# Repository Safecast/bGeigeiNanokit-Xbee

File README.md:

# bGeigieCast

Available at [Link](https://bgeigiezen.safecast.jp/store-2/bgeigienano/)

* An extension module to use your mobile bGeigieNano as a fixed sensor! 
* Adds Wi-Fi and Bluetooth (BLE) to a bGeigieNano.
* Open Source software and Open Source hardware. 
* For real-time reporting/sending data to the Safecast API in fixed and mobile mode.
* Easy to program and change code for other APIs due to the USB-C connector.
* Needs to be soldered together to use it.

User manual and other documentation on the Github Wiki:

* [User manual](https://github.com/Safecast/bGeigieCast/wiki/User-manual)
* [Quick start guide](https://github.com/Safecast/bGeigieCast/wiki/Quick-start-guide)
* [Set up your development environment](https://github.com/Safecast/bGeigieCast/wiki/Development-environment)

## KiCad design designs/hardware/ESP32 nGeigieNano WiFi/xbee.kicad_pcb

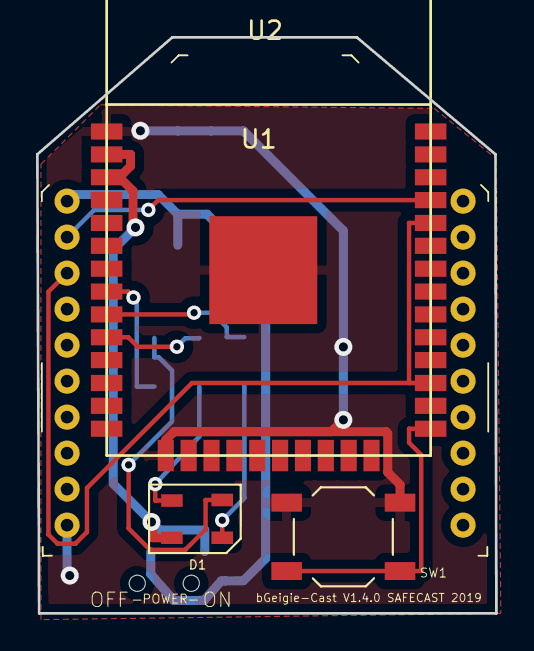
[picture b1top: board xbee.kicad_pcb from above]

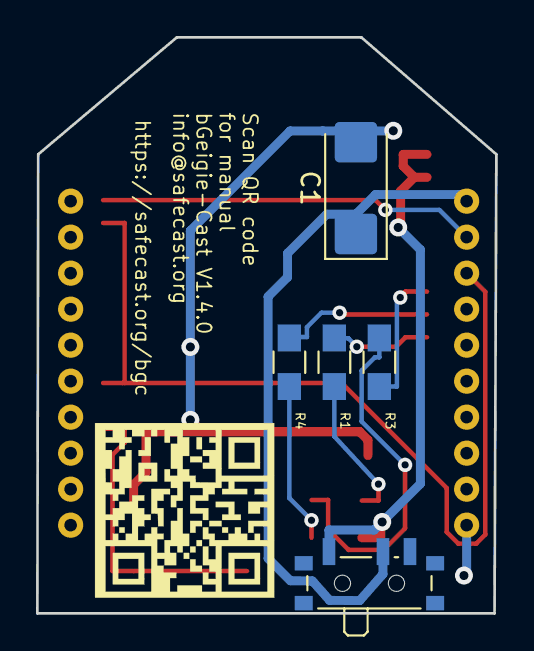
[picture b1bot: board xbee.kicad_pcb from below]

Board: 2 copper layers, 25.5 x 32.0 mm, 9 parts (5 on the bottom side), 12 nets.

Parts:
C1: 330uF; CP_EIA-6032-15_Kemet-U_Pad2.25x2.35mm_HandSolder
D1: RGB-LED; DJS-BRGBC-TR8
R1, R3, R4: 470; R_0805_HandSoldering
SW1: TACT-SWITCH; SW_SPST_TL3342
SW2: SWITCH_INV; SW_SPDT_PCM12
U1: ESP32S; ESP-32S
U2: XBEE-socket; XBEE-20_THT

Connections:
+3V3: D1.2 (K), SW2.1 (A), U1.2 (VCC), U1.3 (EN)
GND: C1.2, SW1.2, U1.1 (GND), U1.15 (GND), U1.39 (GND_PAD), U2.10 (GND)
unnamed: D1.3 (BA), R1.2
unnamed: D1.4 (GA), R3.2
unnamed: D1.1 (RA), R4.2
unnamed: SW1.1, U1.25 (IO0)
unnamed: U1.27 (IO16), U1.34 (RXD0), U2.3 (DIN)
unnamed: R1.1, U1.10 (IO25)
unnamed: R3.1, U1.8 (IO32)
unnamed: R4.1, U1.9 (IO33)
unnamed: U1.35 (TXD0), U2.2 (DOUT)
VDD: C1.1, SW2.2 (B), U2.1 (VDD)

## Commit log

2024-04-30 bGeigieCast M5Stamp
2024-06-14 Updated and cleaned out the board
2024-06-16 update to new library version, improve api connection
2024-11-19 Addded V5 of firmware
2024-11-19 Cleaned up backups
2024-11-19 Updated and cleaned uo V1.6.2 boards
2024-11-19 Exported the Gerber files
